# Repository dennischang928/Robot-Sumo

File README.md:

# Robot-Sumo

## Battery Managment System

### Desired balancing current

#### Wh: 

(I * V)*2 + 1 

where I and V are the current and voltage of a motor at the highest efficiency

- I = 1.5A
- V = 12v

Desired battery capacity:

- 37w * desired working time = 37w * 0.5h = 18.5wh
  - = 1.54Ah (3 cell, 12 volt battery)

Desired balancing current

- For a 1.8Ah Battery
  - Assuming that the cells have less than a 1% charge-time difference at their end of life
    - 1.8Ah * 0.01 = 18mAh
    - With a balancing current of 10mA (internal cell balancing by bq40z80)
      - The cell can be balanced in 1.8 hour

### Cell balancer and gauges

- Gauges with integrated balancer: Bq40z80

## MotherBoard Design

- Low-level hardware control MCU: STM32f103c8t6
  - also could be used to run an onboard algorithm
- **Customized Sensor module: I2C Fast Mode Communication**
  - 400kbits/s
  - 3V3 powered
  - 3V3 SDA SCL GND 
  - data flow: slave(sensor brd) to master(mother brd) **only**
- **Motor Port: I2C Communicaation**
  - **12V powered**
  - **VCC SDA SCL GND (Port)**
- **Edge Sensor**
  - **3V3 powered**
  - **Signal GND VCC *4**
- **12V power port for charging or powering**
- Battery: SMBus Communication
  - **12V battery pack power supply**
  - SMBC SMBD
    - Remaining fuel
    - Battery state (Temp. Storage... etc)
- **12V->5V->3V3**
  - **12V -> 5V**
    - **LM2596-5V buck converter**

  - **5V -> 3V3**
    - **RT9193-33 LDO**

- NRF24

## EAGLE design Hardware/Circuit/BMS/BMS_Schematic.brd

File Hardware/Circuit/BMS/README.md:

# BMS

## List of Material

- JST-4-PTH
- Schottky diode 1N5819HW-7
- Pre-charge PMOS FDS4685
- Reverse polarity protection NMOS AO3400
- PESD12VL1BA

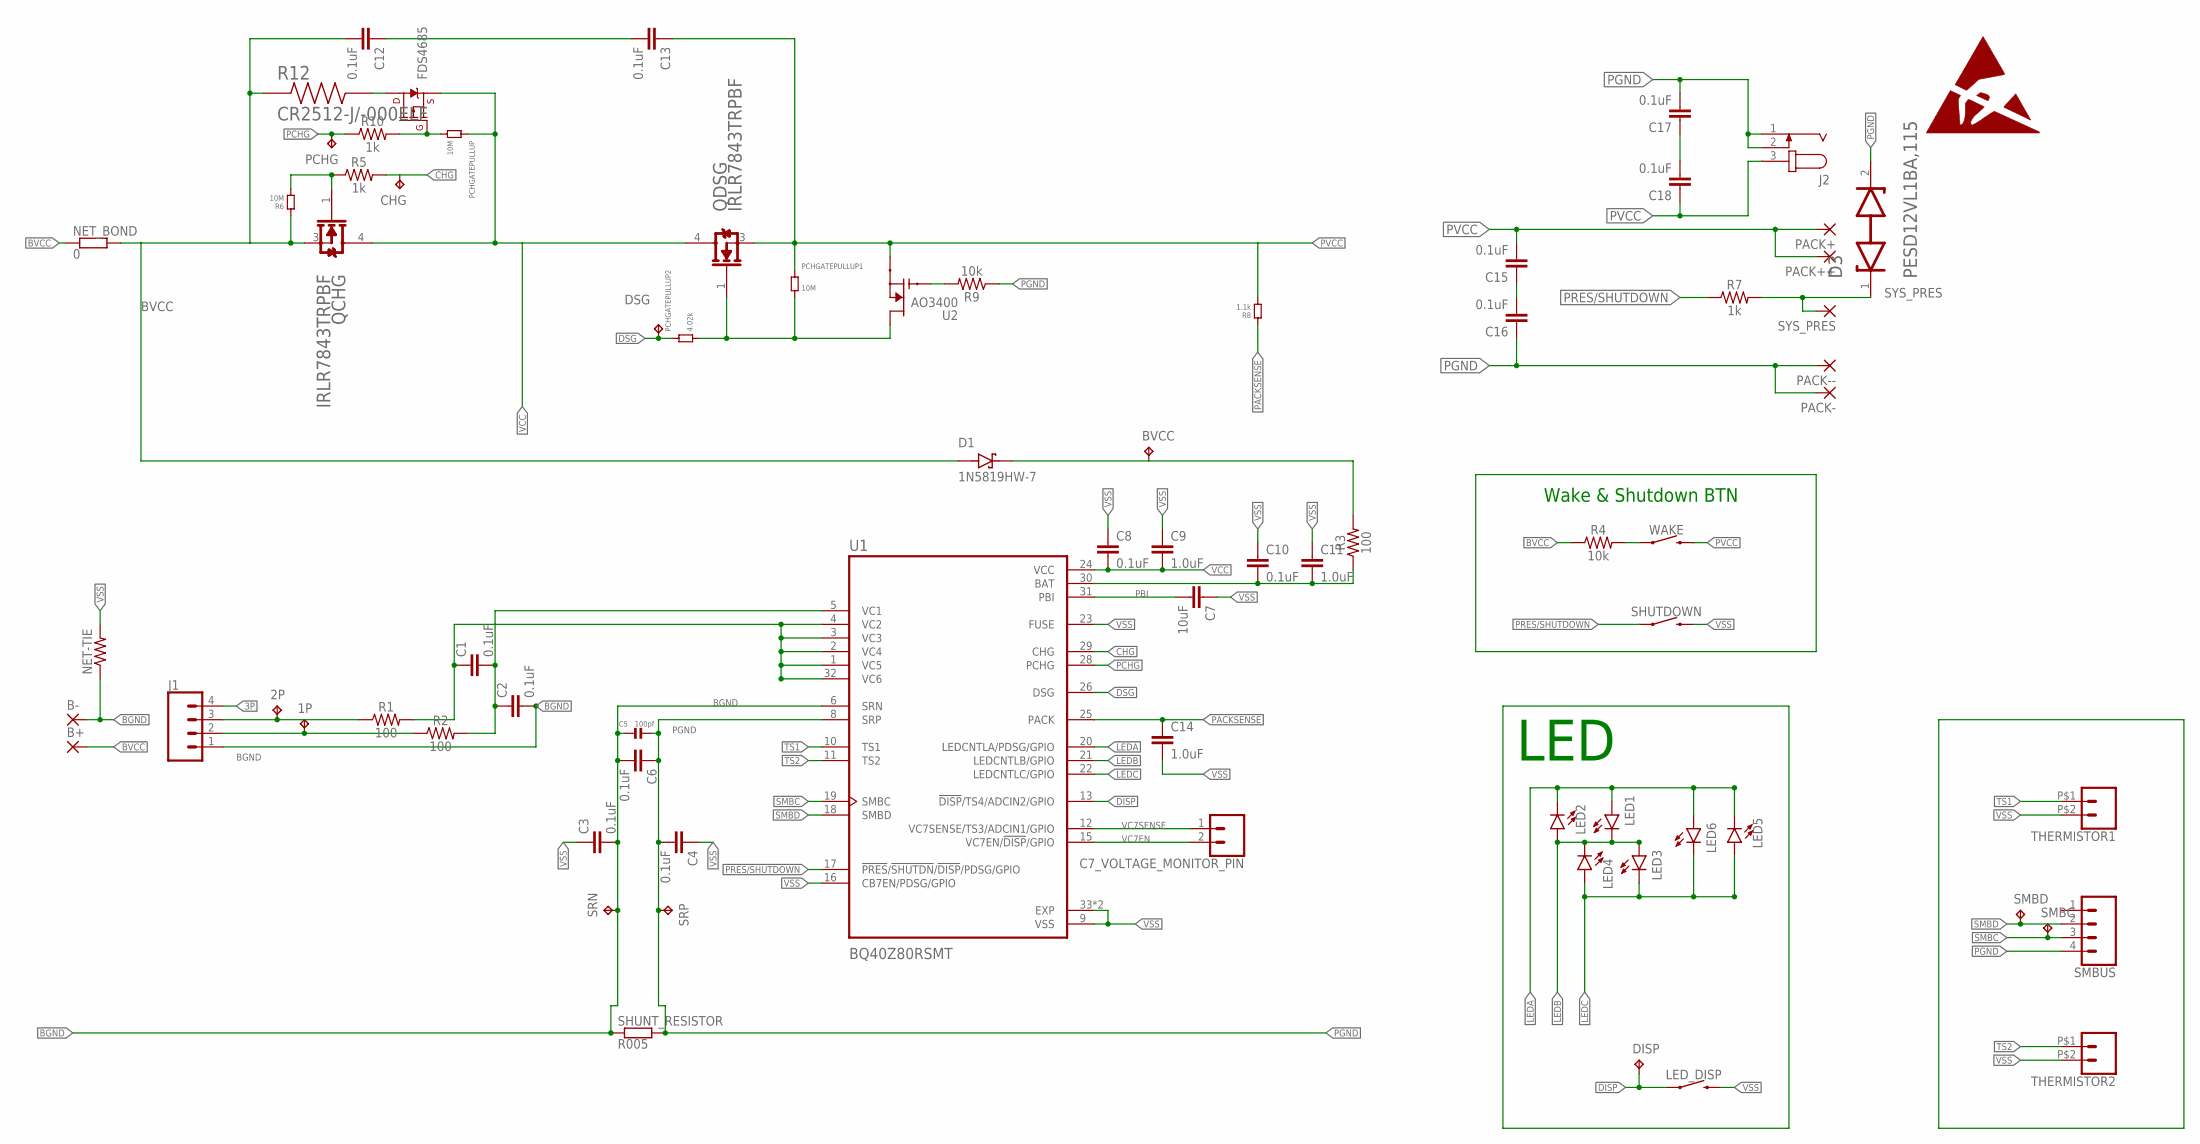
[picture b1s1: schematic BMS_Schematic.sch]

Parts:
1P, 2P: TPTP10R; TP10R
B+: WIREPADSMD5-2,5; 5-2,5
B-: WIREPADSMD5-2,5; 5-2,5
BVCC: TPTP10R; TP10R
C1, C2, C3, C4, C6, C8, C10, C12, C13, C15, C16, C17, C18: 0.1uF; 0603
C5: 100pf; 0805
C7: 10uF; 0603
C7_VOLTAGE_MONITOR_PIN: CONN_02; 1X02
C9, C11, C14: 1.0uF; 0603
CHG: TPTP10R; TP10R
D1: 1N5819HW-7; SOD3715X145N
D3: NEXPERIA_PESD12VL1BA,115NEXPERIA_PESD12VL1BA,115_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; NEXPERIA_PESD12VL1BA,115_0
DISP: TPTP10R; TP10R
DSG: TPTP10R; TP10R
J1: CONN_04JST-PTH; JST-4-PTH
J2: JACK-PLUG0; SPC4077
LED1, LED2, LED3, LED4, LED5, LED6: GREEN; LED-0603
LED_DISP: MOMENTARY-SWITCH-SPST-SMD-6.0X3.5MM; TACTILE_SWITCH_SMD_6.0X3.5MM
NET-TIE: 0; 0402-TIGHT
NET_BOND: 0; BVS
PACK+: WIREPADSMD5-2,5; 5-2,5
PACK++: WIREPADSMD5-2,5; 5-2,5
PACK-: WIREPADSMD5-2,5; 5-2,5
PACK--: WIREPADSMD5-2,5; 5-2,5
PCHG: TPTP10R; TP10R
PCHGATEPULLUP, PCHGATEPULLUP1: 10M; 0805
PCHGATEPULLUP2: 4.02k; 0805
QCHG: INFINEON_IRLR7843TRPBFINFINEON_IRLR7843TRPBF_0_0; INFINEON_IRLR7843TRPBF_0
QDSG: INFINEON_IRLR7843TRPBFINFINEON_IRLR7843TRPBF_0_0; INFINEON_IRLR7843TRPBF_0
R1, R2, R3: 100; 0603
R4, R9: 10k; 0603
R5, R7, R10: 1k; 0603
R6: 10M; 0805
R8: 1.1k; 0805
R12: CR2512-J/-000ELF; RESC6331X75N
SHUNT_RESISTOR: R005; BVS
SHUTDOWN: MOMENTARY-SWITCH-SPST-SMD-6.0X3.5MM; TACTILE_SWITCH_SMD_6.0X3.5MM
SMBC: TPTP10R; TP10R
SMBD: TPTP10R; TP10R
SMBUS: CONN_04JST-SMD-LOCKING; JST-4-SMD-1.25MM-LOCKING
SRN: TPTP10R; TP10R
SRP: TPTP10R; TP10R
SYS_PRES: SMD2; SMD1,27-2,54
THERMISTOR1, THERMISTOR2: SOLDER_PAD_2
U1: BQ40Z80RSMT; QFN40P400X400X100-33N
U2: AO3400; SOT23
U$2: FDS4685; SOIC127P600X150-8N
WAKE: MOMENTARY-SWITCH-SPST-SMD-6.0X3.5MM; TACTILE_SWITCH_SMD_6.0X3.5MM

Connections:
1P: C1.2, C2.1, R2.2, U1.5 (VC1)
2P: C1.1, R1.2, U1.1 (VC5), U1.2 (VC4), U1.3 (VC3), U1.4 (VC2), U1.32 (VC6)
3P: J1.4
BAT: C10.2, C11.2, R3.1, U1.30 (BAT)
BGND: B-.1, C2.2, C3.2, C5.1, C6.2, J1.1, NET-TIE.1, SHUNT_RESISTOR.2, SRN.TP, U1.6 (SRN)
BVCC: B+.1, C12.2, D1.A, NET_BOND.1, NET_BOND.2, QCHG.3 (SOURCE), R4.1, R6.1, R12.1
CHG: CHG.TP, R5.2, U1.29 (CHG)
DISP: DISP.TP, LED_DISP.1, U1.13 (!DISP!/TS4/ADCIN2/GPIO)
DSG: DSG.TP, PCHGATEPULLUP2.1, U1.26 (DSG)
LEDA: LED1.A, LED2.C, LED5.C, LED6.A, U1.20 (LEDCNTLA/PDSG/GPIO)
LEDB: LED1.C, LED2.A, LED3.A, LED4.C, U1.21 (LEDCNTLB/GPIO)
LEDC: LED3.C, LED4.A, LED5.A, LED6.C, U1.22 (LEDCNTLC/GPIO)
unnamed: R9.2, U2.1 (G)
unnamed: 2P.TP, J1.3, R1.1
unnamed: 1P.TP, J1.2, R2.1
unnamed: C12.1, C13.2
unnamed: BVCC.TP, D1.C (K), R3.2
unnamed: R12.2, U$2.5 (D), U$2.6 (D), U$2.7 (D), U$2.8 (D)
unnamed: PCHGATEPULLUP.2, R10.2, U$2.4 (G)
unnamed: QCHG.1 (GATE), R5.1, R6.2
unnamed: PCHGATEPULLUP1.2, PCHGATEPULLUP2.2, QDSG.1 (GATE), U2.3 (D)
unnamed: R4.2, WAKE.1
unnamed: C15.1, C16.2
unnamed: C17.1, C18.2
PACKSENSE: C14.1, R8.1, U1.25 (PACK)
PBI: C7.2, U1.31 (PBI)
PCHG: PCHG.TP, R10.1, U1.28 (PCHG)
PGND: C4.2, C5.2, C6.1, C16.1, C17.2, D3.2 (CATHODE_2), J2.1, J2.2, PACK-.1, PACK--.1, R9.1, SHUNT_RESISTOR.1, SMBUS.4, SRP.TP, U1.8 (SRP)
PRES/SHUTDOWN: R7.1, SHUTDOWN.1, U1.17 (!PRES!/!SHUTDN!/!DISP!/PDSG/GPIO)
PVCC: C13.1, C15.2, C18.1, J2.3, PACK+.1, PACK++.1, PCHGATEPULLUP1.1, QDSG.3 (SOURCE), R8.2, U2.2 (S), WAKE.2
SMBC: SMBC.TP, SMBUS.3, U1.19 (SMBC)
SMBD: SMBD.TP, SMBUS.2, U1.18 (SMBD)
SYS_PRES: D3.1 (CATHODE_1), R7.2, SYS_PRES.1
TS1: THERMISTOR1.P$1 (1), U1.10 (TS1)
TS2: THERMISTOR2.P$1 (1), U1.11 (TS2)
VC7EN: C7_VOLTAGE_MONITOR_PIN.2, U1.15 (VC7EN/!DISP!/GPIO)
VC7SENSE: C7_VOLTAGE_MONITOR_PIN.1, U1.12 (VC7SENSE/TS3/ADCIN1/GPIO)
VCC: C8.2, C9.2, PCHGATEPULLUP.1, QCHG.4 (DRAIN), QDSG.4 (DRAIN), U1.24 (VCC), U$2.1 (S), U$2.2 (S), U$2.3 (S)
VSS: C3.1, C4.1, C7.1, C8.1, C9.1, C10.1, C11.1, C14.2, LED_DISP.2, NET-TIE.2, SHUTDOWN.2, THERMISTOR1.P$2 (2), THERMISTOR2.P$2 (2), U1.9 (VSS), U1.16 (CB7EN/PDSG/GPIO), U1.23 (FUSE), U1.33 (EXP), U1.33_1 (EXP)

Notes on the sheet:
LED
Wake & Shutdown BTN

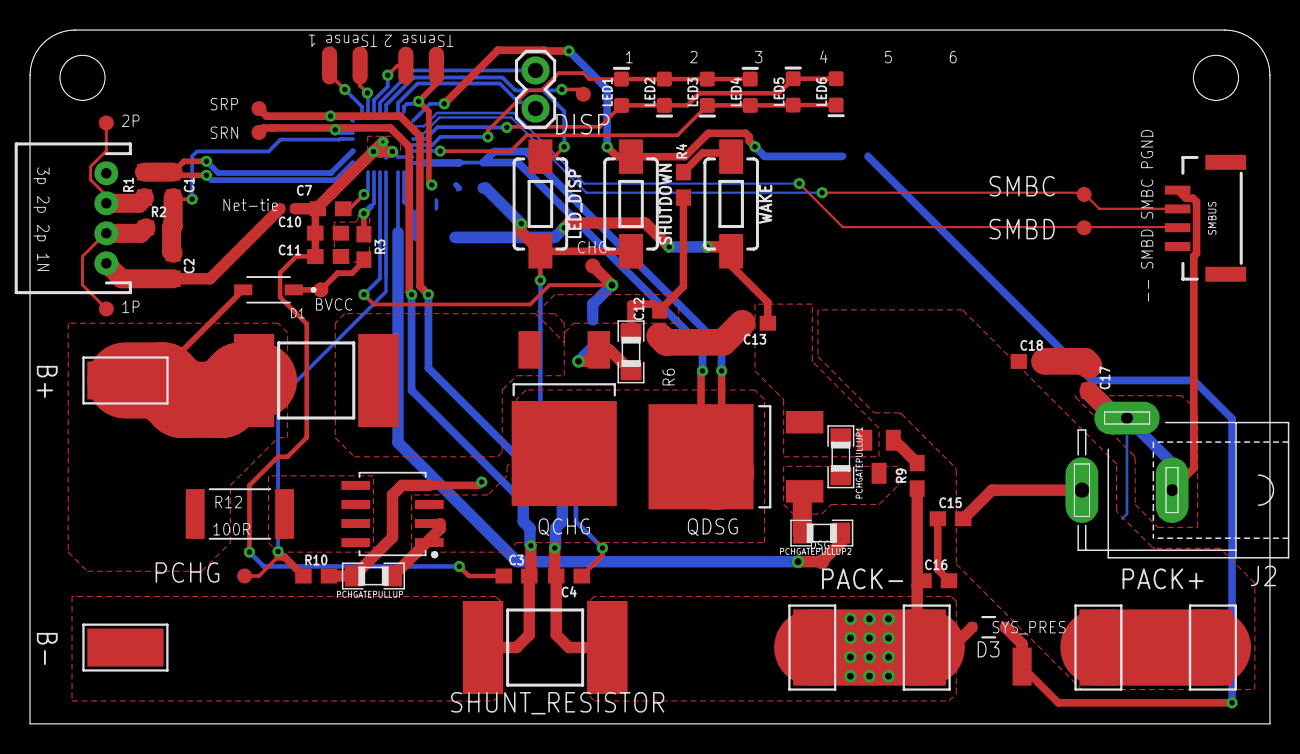
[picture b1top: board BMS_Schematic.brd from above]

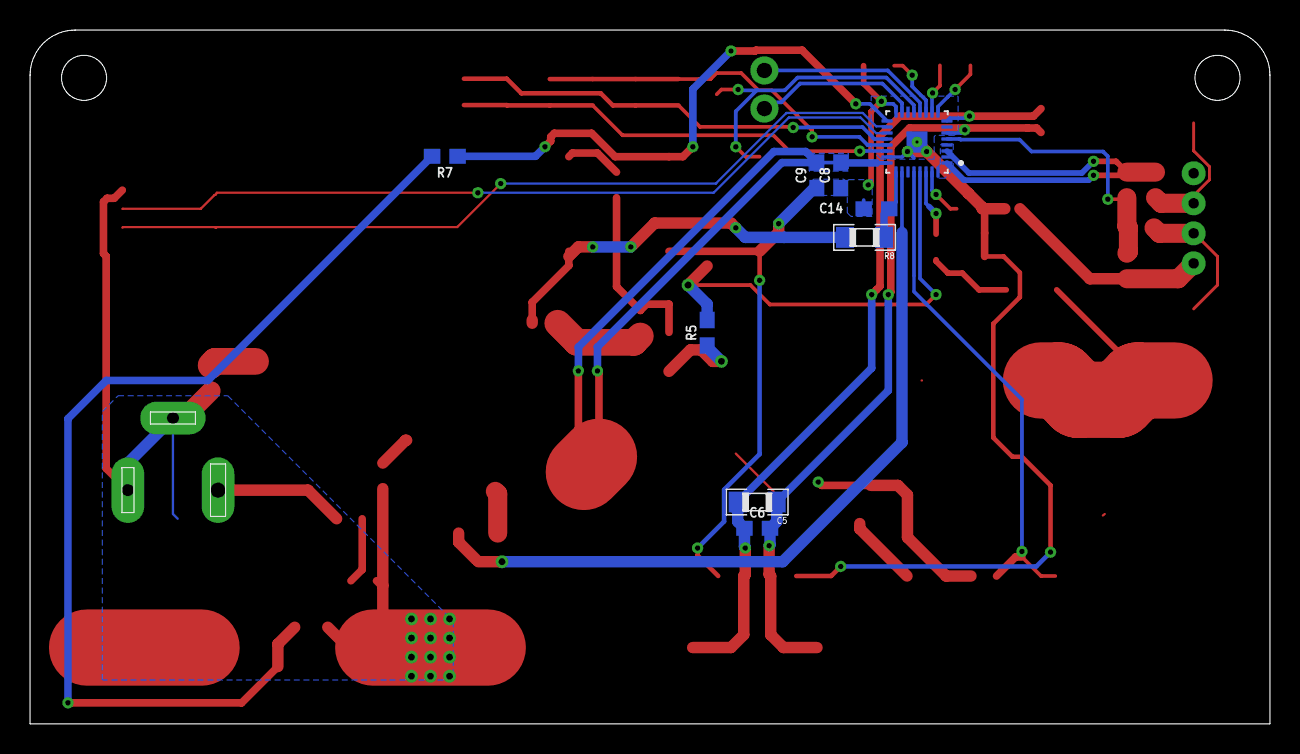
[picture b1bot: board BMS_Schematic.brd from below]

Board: 2 copper layers, 82.5 x 46.2 mm, 75 parts (9 on the bottom side), 38 nets.

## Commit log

2023-05-04 Init the Respitory
2023-05-18 Changing [CAD] directory [Gcode, CNC, STL] position
2023-05-18 Finish designing the robot's gear box
2023-06-10 Finalize B.M.S Mark1 PCB design with all components and connections
2023-08-19 Testing communication between two stm32 inside [MultiMCUsTest] folder, originally planned to use spi as the interface for data transfer. Failed
2023-08-21 Testing communication between two stm32 inside [MultiMCUsTest] folder, failed to use CAN as the interface. Using I2C in the future
2023-08-22 Succeed to test communication between two stm32 inside [MultiMCUsTest] folder with I2C as the interface
2023-08-22 Update README.md
    Update the method of communication between sensorBrd and MotherBrd from SPI simplex to I2C
2023-08-22 Sensor-Mother Brd communciation: succeed to send multi(eight) bytes together
2024-01-31 Project Finalized

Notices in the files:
parts and their libraries:
SparkFun-Connectors: Licensing: Creative Commons ShareAlike 4.0 International - https://creativecommons.org/licenses/by-sa/4.0
